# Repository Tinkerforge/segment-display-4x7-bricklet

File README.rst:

Segment Display 4x7 Bricklet
============================

This repository contains the firmware source code and the hardware design
files. The documentation generator configs can be found at
https://github.com/Tinkerforge/generators

Repository Content
------------------

software/:
 * examples/: Examples for all supported languages
 * build/: Compiled files
 * src/: Source code of firmware
 * Makefile: Makefile to build project

hardware/:
 * Contains KiCad project files and additionally schematics as PDF

datasheets/:
 * Contains datasheets for sensors and complex ICs that are used

Hardware
--------

The hardware is designed with the open source EDA Suite KiCad
(http://www.kicad.org). Before you are able to open the files,
you have to install the Tinkerforge kicad-libraries
(https://github.com/Tinkerforge/kicad-libraries). You can either clone
them directly in hardware/ or clone them in a separate folder and
symlink them into hardware/
(ln -s kicad_path/kicad-libraries project_path/hardware). After that you
can open the .pro file in hardware/ with KiCad and from there view and
modify the schematics and the PCB layout.

Software
--------

If you want to do your own Brick/Bricklet firmware development we highly
recommend that you use our build environment setup script and read the
tutorial (https://www.tinkerforge.com/en/doc/Tutorials/Tutorial_Build_Environment/Tutorial.html).

To compile the C code we recommend you to install the newest GNU Arm Embedded
Toolchain (https://launchpad.net/gcc-arm-embedded/+download).
You also need to install bricklib (https://github.com/Tinkerforge/bricklib)
and brickletlib (https://github.com/Tinkerforge/brickletlib).

You can either clone it directly in software/src/ or clone it in a
separate folder and symlink it into software/src/
(ln -s bricklib_path/bricklib project_path/software/src/ and
ln -s brickletlib_path/brickletlib project_path/software/src/).
Finally make sure to have CMake installed
(http://www.cmake.org/cmake/resources/software.html).

After that you can build the firmware by invoking make in software/.
The firmware (.bin) can then be found in software/build/ and uploaded
with brickv (click button "Flashing" on start screen).

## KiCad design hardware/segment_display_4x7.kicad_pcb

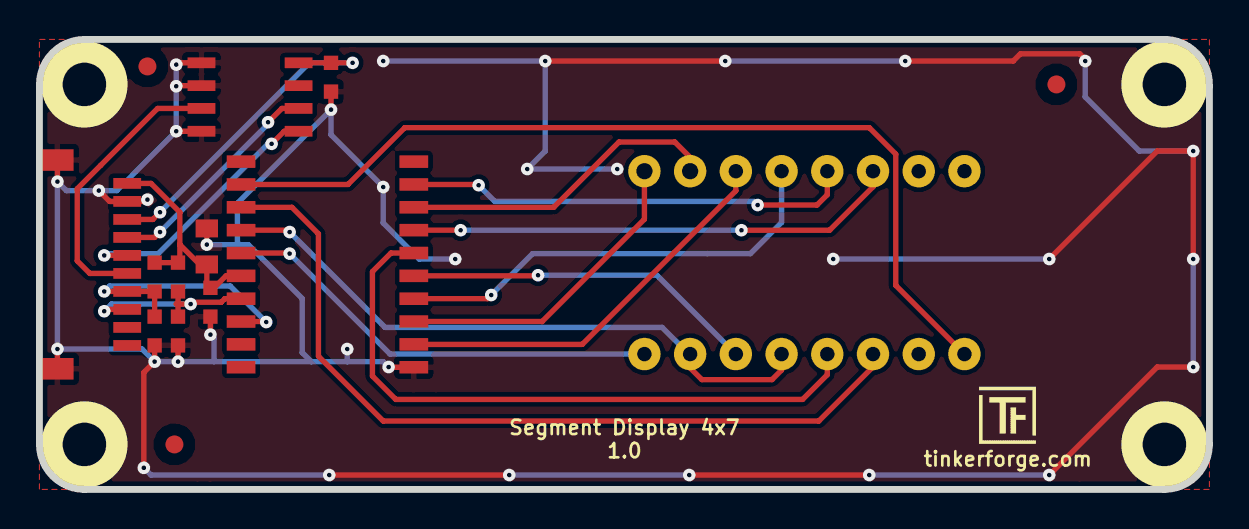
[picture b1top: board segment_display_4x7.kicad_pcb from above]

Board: 2 copper layers, 65.0 x 25.0 mm, 20 parts (0 on the bottom side), 20 nets.

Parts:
C1, C3: 1nF; C0603
C2: 10µF; C0805
C4: 100nF; C0603
C5: 100nF; R0603
Fiducial_Mark: VAL**; Fiducial_Mark
Fiducial_Mark#2, Fiducial_Mark#3: VAL**; Fiducial_Mark
P1: CON-SENSOR
R1, R2: 1k; R0603
U1: M24C64; SOIC8
U2: TM1637; SOP20
U3: SEGMENT_4X7
U4, U5, U6, U7: DRILL; DRILL_NP
VAL: CE_5mm
VAL#2: WEEE_7mm

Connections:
+5V: C2.1, C5.1, P1.1, R1.1, R2.1, U2.16
COM1: U2.15, U3.1
COM2: U2.14, U3.2, U3.4
COM3: U2.13, U3.6
COM4: U2.12, U3.8
GND: C1.1, C2.2, C3.1, C4.2, C5.2, P1.2, P1.EP, U1.1, U1.2, U1.4, U2.1
unnamed: C1.2, P1.7, R1.2, U2.18
unnamed: C3.2, P1.8, R2.2, U2.17
unnamed: P1.4, U1.6
unnamed: P1.5, U1.5
unnamed: P1.6, U1.3
unnamed: U2.2, U3.14
unnamed: U2.3, U3.16
unnamed: U2.4, U3.13
unnamed: U2.5, U3.3
unnamed: U2.6, U3.5
unnamed: U2.7, U3.11
unnamed: U2.8, U3.15
unnamed: U2.9, U3.12
VCC: C4.1, P1.3, U1.8

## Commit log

2013-08-02 Initial commit for Segment Display 4x7 Bricklet
2013-08-21 windows: Don't trigger a build in generate_makefile.bat
    Also use normal make instead of a special named one.
2013-08-30 Add counter API and implementation
2013-09-03 Add datasheet for 7-segment display
2013-09-16 Change segment order (left to right)
2013-09-16 Add examples for Segment Display 4x7 Bricklet
2013-10-15 add hardware files
2013-10-18 Fix name to fit naming convention
2013-11-20 Change pins for newest hardware version
2014-01-06 Add static assert for BrickContext size
2014-01-10 Add Perl examples
2014-01-15 php: Use const for constant values
2014-02-07 Add Mathematica examples
2014-02-10 perl: fixed namespace
2014-02-12 javascript: add examples
2014-02-18 javascript: examples fixed
2014-02-20 javascript: add html exmaples
2014-02-24 javascript: port 4280, startExample()
2014-02-28 javascript: Break long lines and cleanup whitespace
2014-03-05 Add LabVIEW example
2014-03-06 labview: Add examples in LV2010 format
2014-03-27 Add I2C clear bus in constructor
2014-03-27 matlab: add examples
2014-04-02 java: Unify constants style
2014-04-02 perl: Unify print style
2014-04-17 matlab: Remove \n prefix from input line
2014-04-17 matlab: Add parentheses to make pygments happy
2014-07-15 java: Replace System.console() usage with an Eclipse compatible pattern
2014-08-13 Fix whitespace
2014-08-13 Fix whitespace again
2014-12-02 Use ReadLine instead of ReadKey for C# example
2015-02-13 vbnet: Use ReadLine instead of ReadKey
    Because ReadKey doesn't work with a pipe as stdin on the RED Brick.
2015-03-02 windows: Stop cmake from searching for mingw32-make.exe
    Using MinGW Makefiles as generator makes cmake search for mingw32-make.exe
    which might not be installed because GnuWin32's make.exe is used instead.
2015-04-14 Show initial counter value
2015-04-14 Don't strip final zero if counter value is zero
    Before, a counter value zero resulted in all segments being off.
2015-04-14 Turn all segments off on startup
    This ensures that the internal state of the Bricklet matches
    what is actually shown on the display.
2015-04-14 Update changelog and version
2015-07-25 Make JavaScript browser example textarea readonly
2015-07-27 Simplify variable names in examples again
2015-07-29 Reformat changelog
2015-08-07 Use full device class name in Python examples
2015-08-12 Fix minor warnings in C/C++ example
2015-08-14 Cleanup Delphi example
2015-08-17 Whitespace
2015-08-18 Cleanup VB.NET examples
2015-08-19 Cleanup Perl example
2015-09-09 Duplicate cmake call to fix bug during cmake creation
2015-09-30 drc run
2015-09-30 Generator based example cleanup
2015-11-12 matlab: Fix callback handling for R2014a
    http://undocumentedmatlab.com/blog/matlab-callbacks-for-java-events-in-r2014a
2015-11-25 Include date and commit into changelog
2016-01-26 php: Add temperature example
2016-05-18 c: Add missing device destroy call
2016-07-01 Make the change UID comment more explicit
2017-06-02 octave: Use javaObject instead of deprecated java_new
2017-11-06 Add 3d information (final)
2017-11-06 Add 3d model (*.step & *.FCStd)
2017-12-07 mathematica: Also generate .nb files
2018-02-19 javascript: Close div tag correctly
2018-02-20 Cleanup KiCad libraries config
    Ensure LibDir=kicad-libraries and LibName1=tinkerforge.
    Remove special library.
2018-05-11 Rename files
2018-05-24 perl: Use strict in examples
2018-06-25 Use english language datasheet (instead of Chinese)
2018-07-11 Add Makefile with docker support
2018-07-11 Update directory structure and build instructions
2018-07-11 Remove obsolete generate_makefile scripts
2018-11-06 Add rust examples
2018-11-07 rust: Accept host names for ip connection, fix naming inconsistencies
2018-12-14 Add go examples.
2018-12-18 go: Change import path.
2018-12-18 go: Change import path again.
2018-12-20 rust: Reformat examples.
2019-01-24 mqtt: Add examples.
2019-01-24 mqtt: Remove executable bit in example permissions.
2019-01-24 go: Minor example fixes.
2020-01-14 examples: Use python3 input by default.
2020-03-18 rust: Update to new skeleton
2020-04-07 examples: rust: Always block when calling bindings functions.
2020-04-07 examples: rust: Fix merge conflict.
2021-10-25 Update KiCad link
    https://www.kicad.org/blog/2021/10/Avoid-links-to-former-kicad-domain/
2022-07-06 Add license files.

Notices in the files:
hardware/segment_display_4x7.kicad_pcb:
Licensed under CERN OHL v.1.1
Copyright (©) 2013, B.Nordmeyer
Copyright Tinkerforge GmbH 2013.
This documentation describes Open Hardware and is licensed under the
CERN OHL v. 1.1.
